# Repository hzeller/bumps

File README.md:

Bumps
=====

> BeagleBone Universal Multi Pololu Steppers

BeagleBone Black cape for [BeagleG][beagleg-url]; using 5 stepper driver modules
from Pololu.

Bumps is an board to work together with [BeagleG][beagleg-url], a fast
GCode system for CNC/3D printers and one of the first making use of the PRU
of the Beaglebone Black for extremely fast step generation.

Find the current version from June 2015 [shared on OshPark][osh-bumps1]. Or use
the [Gerber files](./gerbers/bumps-gerbers.zip) directly.

### Version History

  * Version 0.1 March 2014 ; 5 Stepper drivers, 2 Power PWMs, 2 small PWM, 2 aux outputs.
  * Version 0.2 June 2015; small revision of otherwise great first board (fix a missing pullup and wrong solder-mask at one place).

### Current work
Work in progress on 0.3 hardware update.

Version 0.3 is work in progress with some changed FETs and other little changes
(see illustration below) but also there is a bigger change
(in branch drv8825-direct) work in progress to directly use the drv8825
drivers without Pololu modules.

Features
   * Simple, mostly passive board with cheap components.
   * Single supply; no separate 5V needed:
      * 5V switching supply to power the BeagleBone from motor voltage (12-36V).
      * Local 3.3V power supply to not put any strain on BBB 3.3V
   * 5 slots for [Pololu-compatible][pololu-url] stepper driver boards.
   * 1 Emergency switch input, directly wired to hardware-reset stepper drivers.
   * 2 high power PWM (Motor voltage, ~20A)
   * 2 Open Collector PWM for smaller loads (Up to 20V, ~2A)
   * 2 Open Collector Auxiliary Outputs (Up to 20V, ~2A)
   * 3 endswitch inputs.
   * 3 temperature sensor inputs.

The following illustrations represent the current work in progress:

![Schematic][schem]
![Board][board]

In real life, the March 2014 version (essentially identical to the June 2015
version):

![Assembled][assembled]

  * Board fabbed by http://oshpark.com/
  * Solder paste dispensed with http://github.com/jerkey 's 3D printer, using
	a program to translate a KiCAD file to GCode (https://github.com/hzeller/rpt2paste )
	.. the whole thing made it to Hackaday:
	http://hackaday.com/2014/04/02/dispensing-solder-paste-with-a-3d-printer/
  * Assembled using a self-made vacuum tweezer
	https://plus.google.com/u/0/+HennerZeller/posts/b3NbB7NzQcM
  * Early test of the system http://youtu.be/hIEY9077D64

[beagleg-url]: https://github.com/hzeller/beagleg
[pololu-url]: http://www.pololu.com/product/1182
[schem]: https://github.com/hzeller/bumps/raw/master/img/bumps-schem.png
[board]: https://github.com/hzeller/bumps/raw/master/img/bumps-board.png
[assembled]: https://github.com/hzeller/bumps/raw/master/img/bumps-connect.jpg
[osh-bumps1]: https://oshpark.com/shared_projects/zIXfRqDE

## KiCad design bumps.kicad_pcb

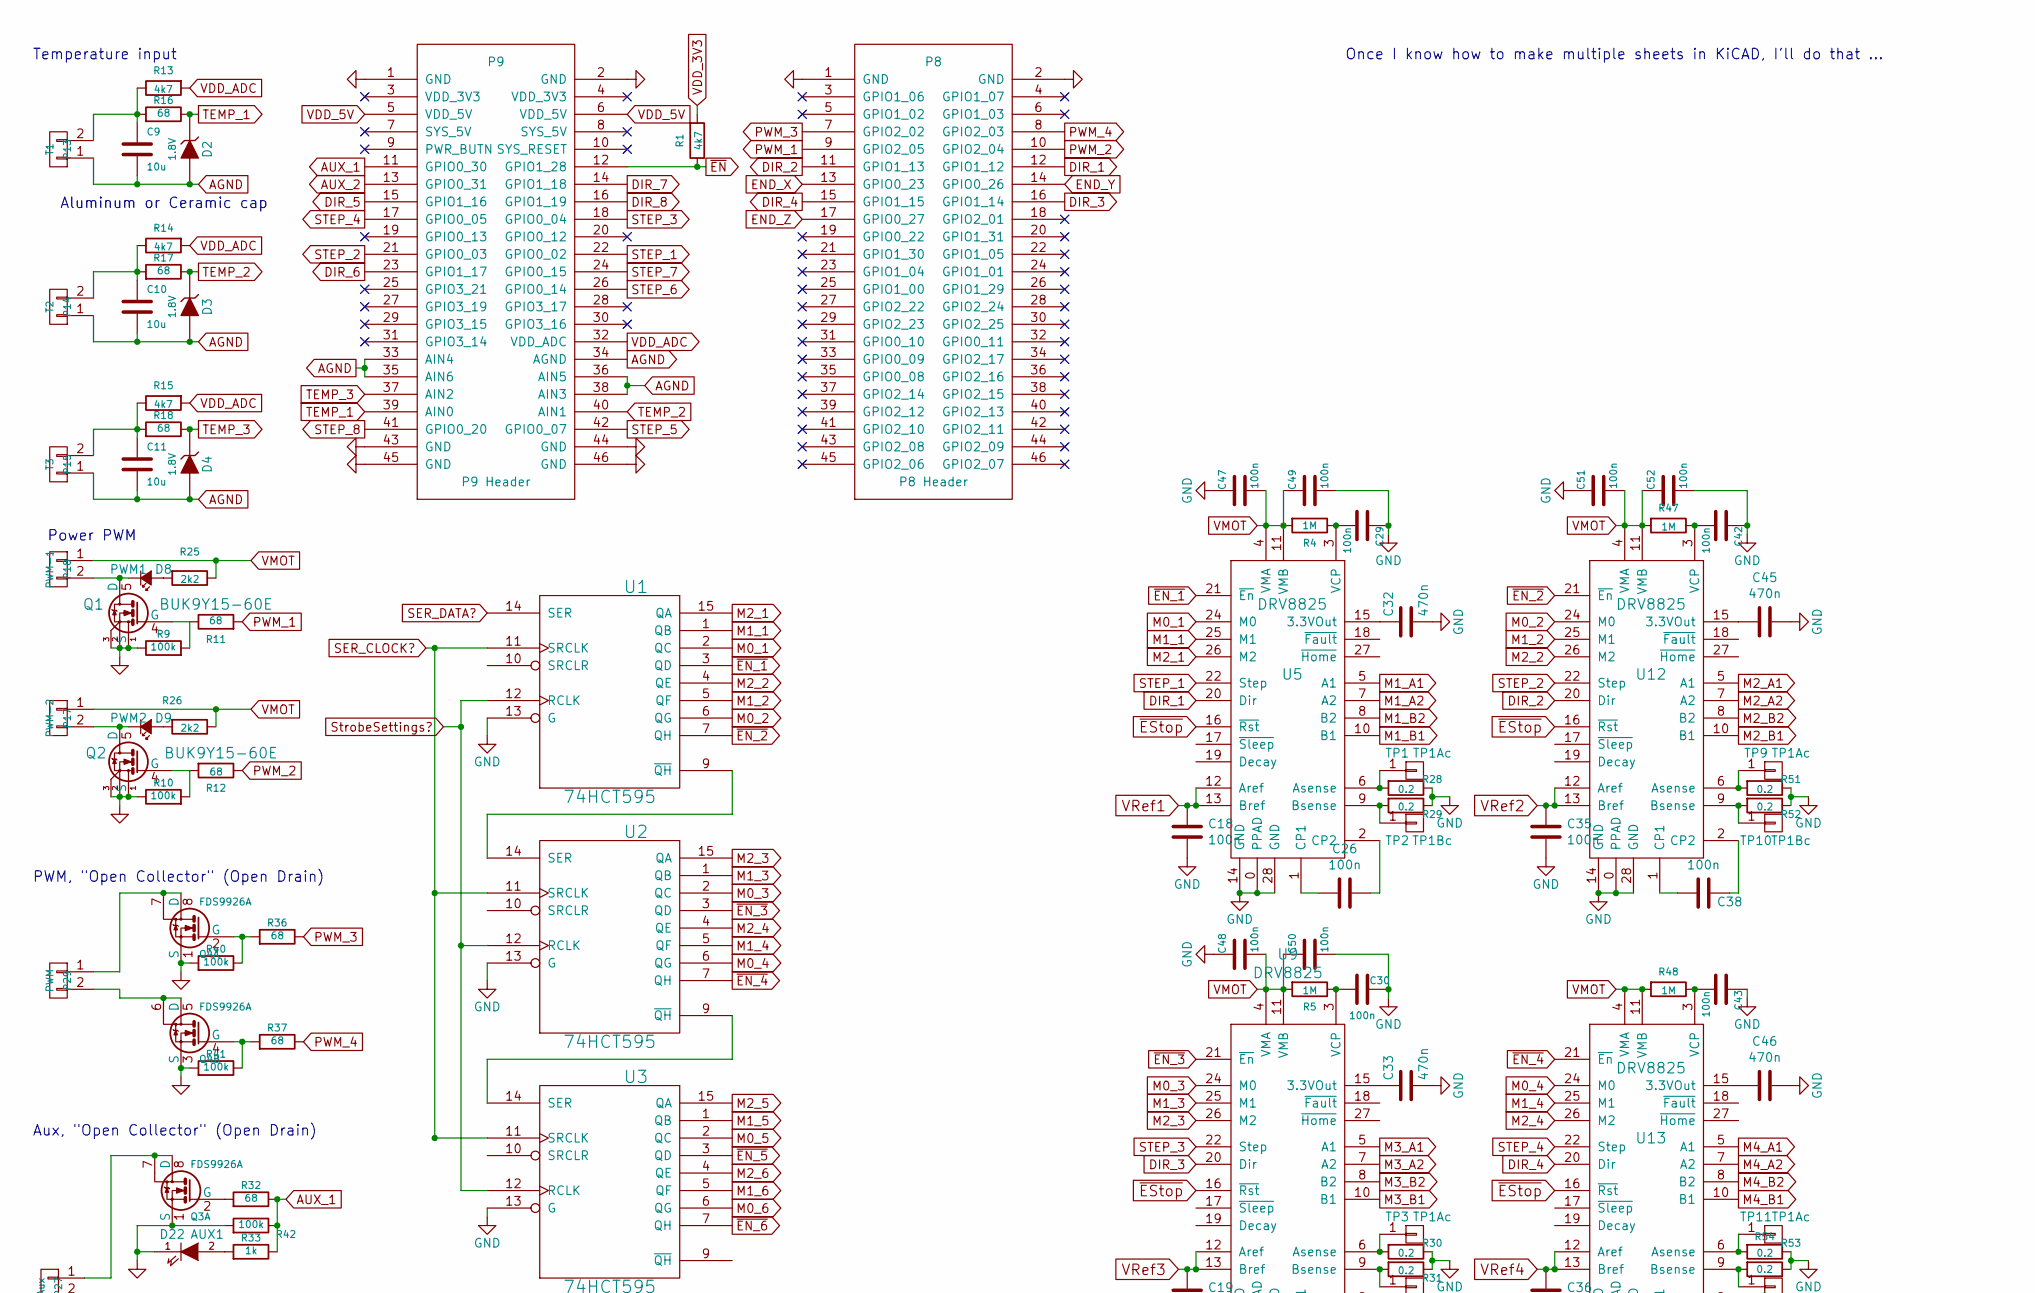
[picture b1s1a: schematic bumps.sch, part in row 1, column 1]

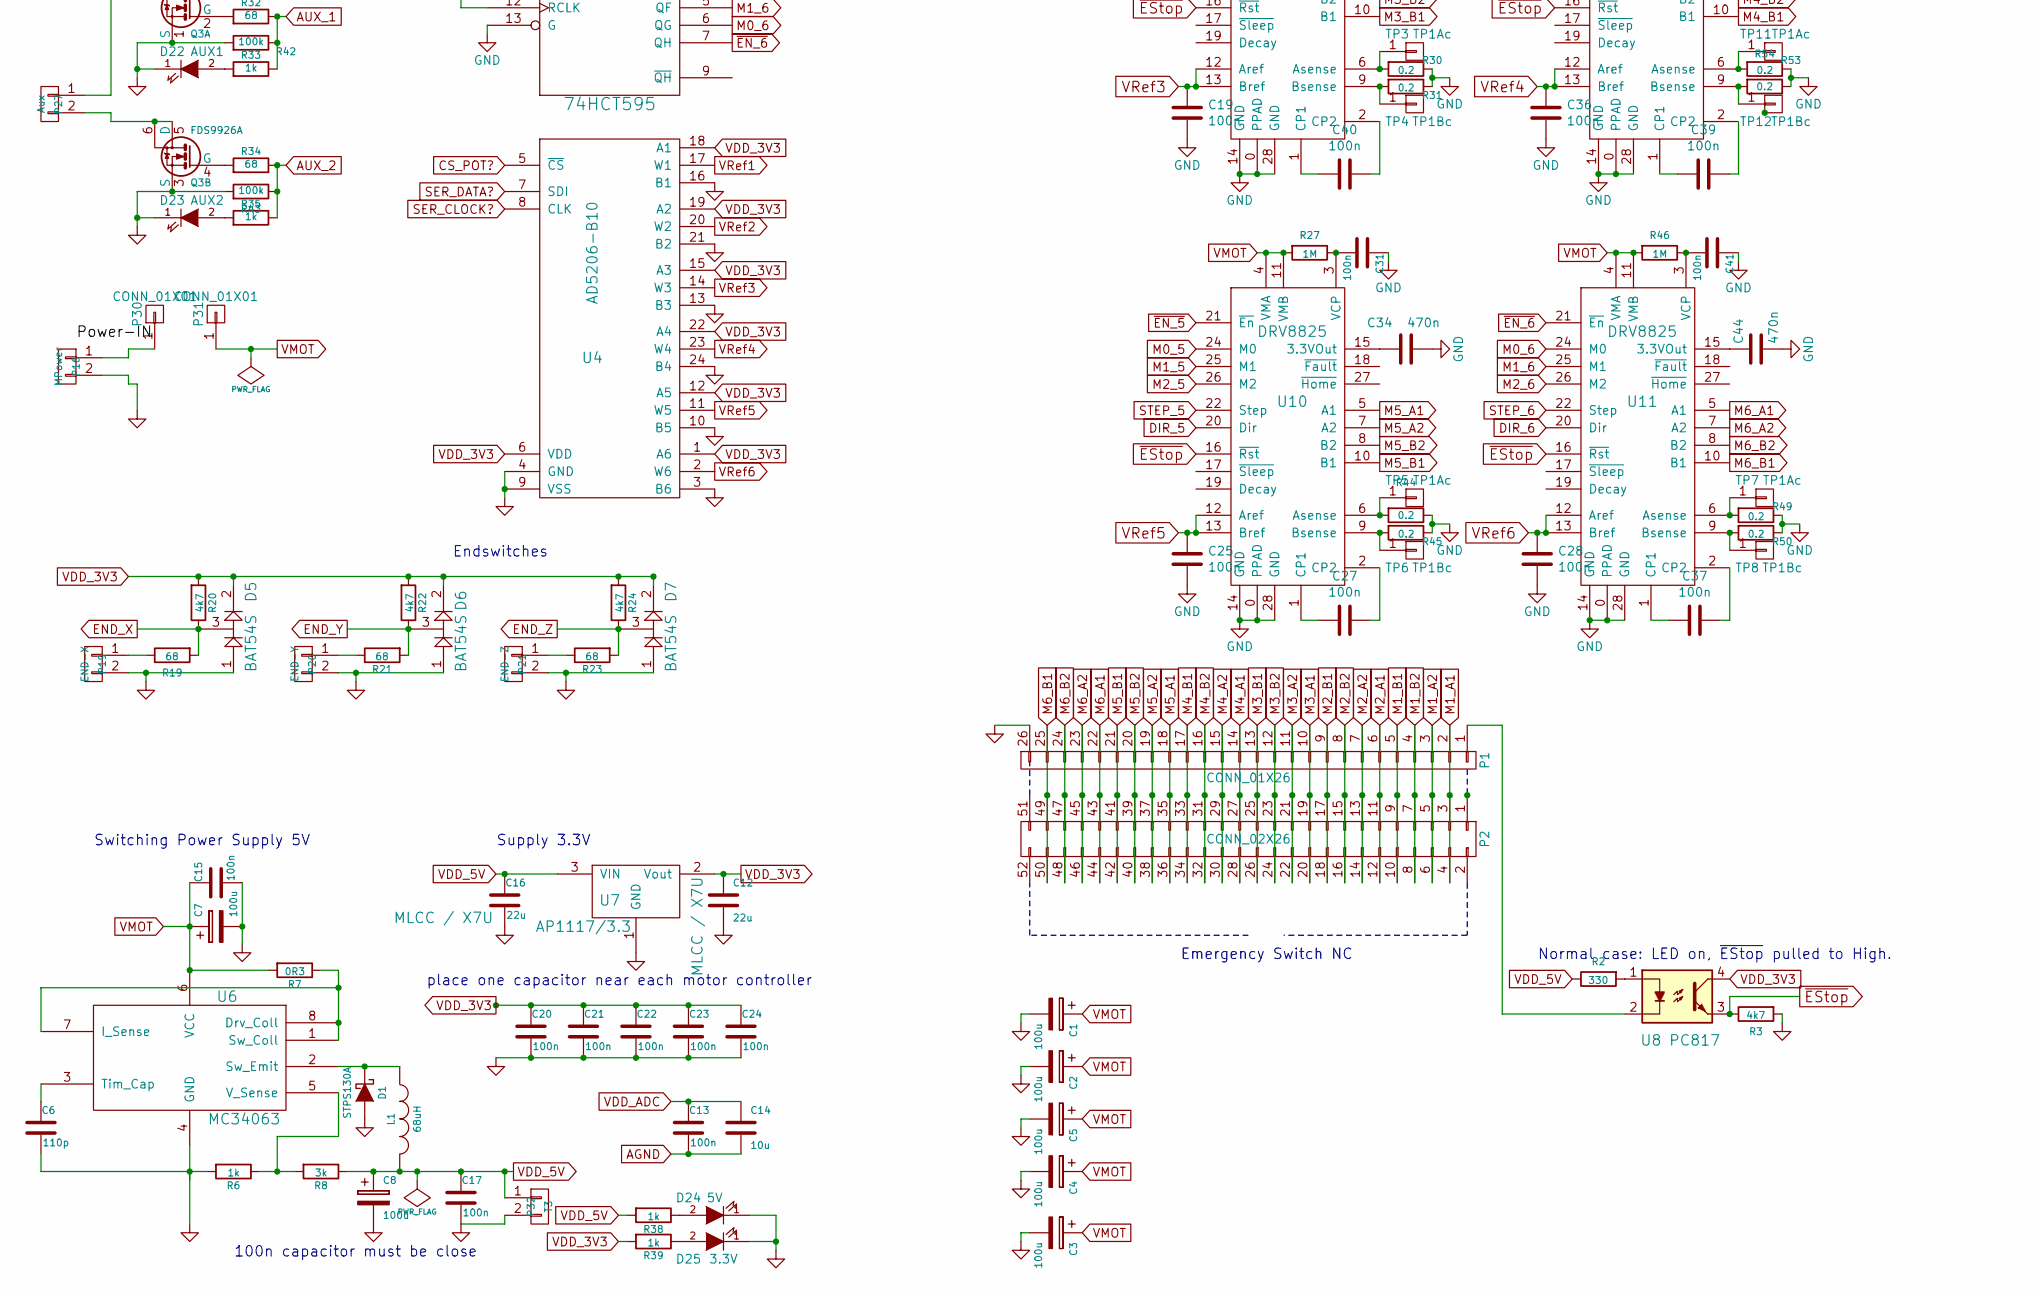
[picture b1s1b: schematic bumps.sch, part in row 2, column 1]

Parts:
C1, C2, C3, C4, C5, C7: 100u; c_elec_6.3x7.7
C6: 110p; C_0805
C8: 100u; C_1206
C9, C10, C11, C14: 10u; C_0805
C12, C16: 22u; C_1206
C13, C15, C17, C20, C21, C22, C23, C24: 100n; C_0805
C18, C19, C25, C26, C27, C28, C29, C30, C31, C35, C36, C37, C38, C39, C40, C41, C42, C43, C47, C48, C49, C50, C51, C52: 100n; C_0603
C32, C33, C34, C44, C45, C46: 470n; C_0603
D1: STPS130A; Diode-SMA_Standard
D2, D3, D4: 1.8V; SOD-123
D5, D6, D7: BAT54S; SOT-23
D8: PWM1; LED-0805
D9: PWM2; LED-0805
D22: AUX1; LED-0805
D23: AUX2; LED-0805
D24: 5V; LED-0805
D25: 3.3V; LED-0805
L1: 68uH; INDUCTOR_V; DigiKey RLB0914-680KL
P1: CONN_01X26; Pin_Header_Straight_1x26
P2: CONN_02X26; Pin_Header_Straight_2x26
P8: P8 Header; PIN_ARRAY_23X2
P9: P9 Header; PIN_ARRAY_23X2
P13: T1; Pin_Header_Straight_1x02
P14: T2; Pin_Header_Straight_1x02
P15, P32: T3; Pin_Header_Straight_1x02
P16: MPower; AK300-2
P17: PWM-2; AK300-2
P18: PWM-1; AK300-2
P19: END-X; Pin_Header_Straight_1x02
P20: END-Y; Pin_Header_Straight_1x02
P21: END-Z; Pin_Header_Straight_1x02
P27: Aux; Pin_Header_Straight_1x02
P29: PWM; Pin_Header_Straight_1x02
P30, P31: CONN_01X01; FuseBlade
Q1, Q2: BUK9Y15-60E; SOT-669_LFPAK_ThermalVias-1
Q3, Q4: FDS9926A; SOIC-8_3.9x4.9mm_Pitch1.27mm
R1, R3, R13, R14, R15, R20, R22, R24: 4k7; R_0805
R2: 330; R_0805
R4, R5, R27, R46, R47, R48: 1M; R_0603
R6, R33, R35, R38, R39: 1k; R_0805
R7: 0R3; R_0805
R8: 3k; R_0805
R9, R10, R40, R41, R42, R43: 100k; R_0805
R11, R12, R16, R17, R18, R19, R21, R23, R32, R34, R36, R37: 68; R_0805
R25, R26: 2k2; R_0805
R28, R29, R30, R31, R44, R45, R49, R50, R51, R52, R53, R54: 0.2; R_1206
TP1, TP3, TP5, TP7, TP9, TP11: TP1Ac; TP
TP2, TP4, TP6, TP8, TP10, TP12: TP1Bc; TP
U1, U2, U3: 74HCT595; TSSOP-16_4.4x5mm_Pitch0.65mm
U4: AD5206-B10; TSSOP-24_4.4x7.8mm_Pitch0.65mm
U5, U9, U10, U11, U12, U13: DRV8825; HTSSOP-28_4.4x9.7mm_Pitch0.65mm
U6: MC34063; SOIC-8_3.9x4.9mm_Pitch1.27mm
U7: AP1117/3.3; SOT-223-3
U8: PC817; DIP-4_W7.62mm

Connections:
AGND: C9.2, C10.2, C11.2, C13.2, C14.2, D2.2 (A), D3.2 (A), D4.2 (A), P9.33 (AIN4), P9.34 (AGND), P9.35 (AIN6), P9.36 (AIN5), P9.38 (AIN3), P13.1, P14.1, P15.1
AUX_1: P9.11 (GPIO0_30), R32.1, R33.1, R42.1
AUX_2: P9.13 (GPIO0_31), R34.1, R35.1, R43.1
DIR_1: P8.12 (GPIO1_12), U5.20 (Dir)
DIR_2: P8.11 (GPIO1_13), U12.20 (Dir)
DIR_3: P8.16 (GPIO1_14), U9.20 (Dir)
DIR_4: P8.15 (GPIO1_15), U13.20 (Dir)
DIR_5: P9.15 (GPIO1_16), U10.20 (Dir)
DIR_6: P9.23 (GPIO1_17), U11.20 (Dir)
END_X: D5.3, P8.13 (GPIO0_23), R19.2, R20.1
END_Y: D6.3, P8.14 (GPIO0_26), R21.2, R22.1
END_Z: D7.3, P8.17 (GPIO0_27), R23.2, R24.1
GND: C1.2, C2.2, C3.2, C4.2, C5.2, C6.2, C7.2, C8.2, C12.2, C15.2, C16.2, C17.2, C18.2, C19.2, C20.2, C21.2, C22.2, C23.2, C24.2, C25.1, C28.1, C29.1, C30.1, C31.1, C32.2, C33.2, C34.2, C35.1, C36.2, C41.1, C42.1, C43.1, C44.2, C45.2, C46.2, C47.1, C48.1, C49.2, C50.2, C51.1, C52.2, D1.2 (A), D5.1, D6.1, D7.1, D22.1 (K), D23.1 (K), D24.1 (K), D25.1 (K), P1.26, P8.1 (GND), P8.2 (GND), P9.1 (GND), P9.2 (GND), P9.43 (GND), P9.44 (GND), P9.45 (GND), P9.46 (GND), P16.2, P19.2, P20.2, P21.2, P32.2, Q1.1 (S), Q1.2, Q1.3, Q2.1 (S), Q2.2, Q2.3, Q3.1 (S), Q3.3 (S), Q4.1 (S), Q4.3 (S), R3.2, R6.2, R9.1, R10.1, R28.1, R29.1, R30.1, R31.1, R40.2, R41.2, R42.2, R43.2, R44.1, R45.1, R49.1, R50.1, R51.1, R52.1, R53.1, R54.1, U1.8 (GND), U1.13 (G), U2.8 (GND), U2.13 (G), U3.8 (GND), U3.13 (G), U4.3 (B6), U4.4 (GND), U4.9 (VSS), U4.10 (B5), U4.13 (B3), U4.16 (B1), U4.21 (B2), U4.24 (B4), U5.0 (PPAD), U5.14 (GND), U5.28 (GND), U6.4 (GND), U7.1 (GND), U9.0 (PPAD), U9.14 (GND), U9.28 (GND), U10.0 (PPAD), U10.14 (GND), U10.28 (GND), U11.0 (PPAD), U11.14 (GND), U11.28 (GND), U12.0 (PPAD), U12.14 (GND), U12.28 (GND), U13.0 (PPAD), U13.14 (GND), U13.28 (GND)
M0_1: U1.2 (QC), U5.24 (M0)
M0_2: U1.6 (QG), U12.24 (M0)
M0_3: U2.2 (QC), U9.24 (M0)
M0_4: U2.6 (QG), U13.24 (M0)
M0_5: U3.2 (QC), U10.24 (M0)
M0_6: U3.6 (QG), U11.24 (M0)
M1_1: U1.1 (QB), U5.25 (M1)
M1_2: U1.5 (QF), U12.25 (M1)
M1_3: U2.1 (QB), U9.25 (M1)
M1_4: U2.5 (QF), U13.25 (M1)
M1_5: U3.1 (QB), U10.25 (M1)
M1_6: U3.5 (QF), U11.25 (M1)
M1_A1: P1.2, P2.3, P2.4, U5.5 (A1)
M1_A2: P1.3, P2.5, P2.6, U5.7 (A2)
M1_B1: P1.5, P2.9, P2.10, U5.10 (B1)
M1_B2: P1.4, P2.7, P2.8, U5.8 (B2)
M2_1: U1.15 (QA), U5.26 (M2)
M2_2: U1.4 (QE), U12.26 (M2)
M2_3: U2.15 (QA), U9.26 (M2)
M2_4: U2.4 (QE), U13.26 (M2)
M2_5: U3.15 (QA), U10.26 (M2)
M2_6: U3.4 (QE), U11.26 (M2)
M2_A1: P1.6, P2.11, P2.12, U12.5 (A1)
M2_A2: P1.7, P2.13, P2.14, U12.7 (A2)
M2_B1: P1.9, P2.17, P2.18, U12.10 (B1)
M2_B2: P1.8, P2.15, P2.16, U12.8 (B2)
M3_A1: P1.10, P2.19, P2.20, U9.5 (A1)
M3_A2: P1.11, P2.21, P2.22, U9.7 (A2)
M3_B1: P1.13, P2.25, P2.26, U9.10 (B1)
M3_B2: P1.12, P2.23, P2.24, U9.8 (B2)
M4_A1: P1.14, P2.27, P2.28, U13.5 (A1)
M4_A2: P1.15, P2.29, P2.30, U13.7 (A2)
M4_B1: P1.17, P2.33, P2.34, U13.10 (B1)
M4_B2: P1.16, P2.31, P2.32, U13.8 (B2)
M5_A1: P1.18, P2.35, P2.36, U10.5 (A1)
M5_A2: P1.19, P2.37, P2.38, U10.7 (A2)
M5_B1: P1.21, P2.41, P2.42, U10.10 (B1)
M5_B2: P1.20, P2.39, P2.40, U10.8 (B2)
M6_A1: P1.22, P2.43, P2.44, U11.5 (A1)
M6_A2: P1.23, P2.45, P2.46, U11.7 (A2)
M6_B1: P1.25, P2.49, P2.50, U11.10 (B1)
M6_B2: P1.24, P2.47, P2.48, U11.8 (B2)
unnamed: C6.1, U6.3 (Tim_Cap)
unnamed: C9.1, P13.2, R13.1, R16.2
unnamed: C10.1, P14.2, R14.1, R17.2
unnamed: C11.1, P15.2, R15.1, R18.2
unnamed: C26.1, U5.2 (CP2)
unnamed: C26.2, U5.1 (CP1)
unnamed: C27.1, U10.2 (CP2)
unnamed: C27.2, U10.1 (CP1)
unnamed: C29.2, R4.1, U5.3 (VCP)
unnamed: C30.2, R5.1, U9.3 (VCP)
unnamed: C31.2, R27.1, U10.3 (VCP)
unnamed: C32.1, U5.15 (3.3VOut)
unnamed: C33.1, U9.15 (3.3VOut)
unnamed: C34.1, U10.15 (3.3VOut)
unnamed: C37.1, U11.1 (CP1)
unnamed: C37.2, U11.2 (CP2)
unnamed: C38.1, U12.2 (CP2)
unnamed: C38.2, U12.1 (CP1)
unnamed: C39.1, U13.1 (CP1)
unnamed: C39.2, U13.2 (CP2)
unnamed: C40.1, U9.1 (CP1)
unnamed: C40.2, U9.2 (CP2)
unnamed: C41.2, R46.1, U11.3 (VCP)
unnamed: C42.2, R47.1, U12.3 (VCP)
unnamed: C43.2, R48.1, U13.3 (VCP)
unnamed: C44.1, U11.15 (3.3VOut)
unnamed: C45.1, U12.15 (3.3VOut)
unnamed: C46.1, U13.15 (3.3VOut)
unnamed: D1.1 (K), L1.1, U6.2 (Sw_Emit)
unnamed: D8.1 (K), P18.2, Q1.5 (D)
unnamed: D8.2 (A), R25.2
unnamed: D9.1 (K), P17.2, Q2.5 (D)
unnamed: D9.2 (A), R26.2
unnamed: D22.2 (A), R33.2
unnamed: D23.2 (A), R35.2
unnamed: D24.2 (A), R38.1
unnamed: D25.2 (A), R39.1
unnamed: P1.1, U8.2
unnamed: P16.1, P30.1
unnamed: P19.1, R19.1
unnamed: P20.1, R21.1
unnamed: P21.1, R23.1
unnamed: P27.1, Q3.7, Q3.8 (D)
unnamed: P27.2, Q3.5 (D), Q3.6
unnamed: P29.1, Q4.7, Q4.8 (D)
unnamed: P29.2, Q4.5 (D), Q4.6
unnamed: Q1.4 (G), R9.2, R11.1
unnamed: Q2.4 (G), R10.2, R12.2
unnamed: Q3.2 (G), R32.2
unnamed: Q3.4 (G), R34.2
unnamed: Q4.2 (G), R36.2, R40.1
unnamed: Q4.4 (G), R37.2, R41.1
unnamed: R2.2, U8.1
unnamed: R6.1, R8.2, U6.5 (V_Sense)
unnamed: R7.1, U6.1 (Sw_Coll), U6.7 (I_Sense), U6.8 (Drv_Coll)
unnamed: R28.2, TP1.1, U5.6 (Asense)
unnamed: R29.2, TP2.1, U5.9 (Bsense)
unnamed: R30.2, TP3.1, U9.6 (Asense)
unnamed: R31.2, TP4.1, U9.9 (Bsense)
unnamed: R44.2, TP5.1, U10.6 (Asense)
unnamed: R45.2, TP6.1, U10.9 (Bsense)
unnamed: R49.2, TP7.1, U11.6 (Asense)
unnamed: R50.2, TP8.1, U11.9 (Bsense)
unnamed: R51.2, TP9.1, U12.6 (Asense)
unnamed: R52.2, TP10.1, U12.9 (Bsense)
unnamed: R53.2, TP11.1, U13.6 (Asense)
unnamed: R54.2, TP12.1, U13.9 (Bsense)
unnamed: U1.9 (~QH), U2.14 (SER)
unnamed: U2.9 (~QH), U3.14 (SER)
PWM_1: P8.9 (GPIO2_05), R11.2
PWM_2: P8.10 (GPIO2_04), R12.1
PWM_3: P8.7 (GPIO2_02), R36.1
PWM_4: P8.8 (GPIO2_03), R37.1
SER_CLOCK?: U1.11 (SRCLK), U2.11 (SRCLK), U3.11 (SRCLK), U4.8 (CLK)
SER_DATA?: U1.14 (SER), U4.7 (SDI)
STEP_1: P9.22 (GPIO0_02), U5.22 (Step)
STEP_2: P9.21 (GPIO0_03), U12.22 (Step)
STEP_3: P9.18 (GPIO0_04), U9.22 (Step)
STEP_4: P9.17 (GPIO0_05), U13.22 (Step)
STEP_5: P9.42 (GPIO0_07), U10.22 (Step)
STEP_6: P9.26 (GPIO0_14), U11.22 (Step)
StrobeSettings?: U1.12 (RCLK), U2.12 (RCLK), U3.12 (RCLK)
TEMP_1: D2.1 (K), P9.39 (AIN0), R16.1
TEMP_2: D3.1 (K), P9.40 (AIN1), R17.1
TEMP_3: D4.1 (K), P9.37 (AIN2), R18.1
VCC: U1.16 (VCC), U2.16 (VCC), U3.16 (VCC)
VDD_3V3: C12.1, C20.1, C21.1, C22.1, C23.1, C24.1, D5.2, D6.2, D7.2, R1.2, R20.2, R22.2, R24.2, R39.2, U4.1 (A6), U4.6 (VDD), U4.12 (A5), U4.15 (A3), U4.18 (A1), U4.19 (A2), U4.22 (A4), U7.2 (Vout), U8.4
VDD_5V: C8.1, C16.1, C17.1, L1.2, P9.5 (VDD_5V), P9.6 (VDD_5V), P32.1, R2.1, R8.1, R38.2, U7.3 (VIN)
VDD_ADC: C13.1, C14.1, P9.32 (VDD_ADC), R13.2, R14.2, R15.2
VMOT: C1.1, C2.1, C3.1, C4.1, C5.1, C7.1, C15.1, C47.2, C48.2, C49.1, C50.1, C51.2, C52.1, P17.1, P18.1, P31.1, R4.2, R5.2, R7.2, R25.1, R26.1, R27.2, R46.2, R47.2, R48.2, U5.4 (VMA), U5.11 (VMB), U6.6 (VCC), U9.4 (VMA), U9.11 (VMB), U10.4 (VMA), U10.11 (VMB), U11.4 (VMA), U11.11 (VMB), U12.4 (VMA), U12.11 (VMB), U13.4 (VMA), U13.11 (VMB)
VRef1: C18.1, U4.17 (W1), U5.12 (Aref), U5.13 (Bref)
VRef2: C35.2, U4.20 (W2), U12.12 (Aref), U12.13 (Bref)
VRef3: C19.1, U4.14 (W3), U9.12 (Aref), U9.13 (Bref)
VRef4: C36.1, U4.23 (W4), U13.12 (Aref), U13.13 (Bref)
VRef5: C25.2, U4.11 (W5), U10.12 (Aref), U10.13 (Bref)
VRef6: C28.2, U4.2 (W6), U11.12 (Aref), U11.13 (Bref)
~EN: P9.12 (GPIO1_28), R1.1
~EN_1: U1.3 (QD), U5.21 (~En)
~EN_2: U1.7 (QH), U12.21 (~En)
~EN_3: U2.3 (QD), U9.21 (~En)
~EN_4: U2.7 (QH), U13.21 (~En)
~EN_5: U3.3 (QD), U10.21 (~En)
~EN_6: U3.7 (QH), U11.21 (~En)
~EStop: R3.1, U5.16 (~Rst), U8.3, U9.16 (~Rst), U10.16 (~Rst), U11.16 (~Rst), U12.16 (~Rst), U13.16 (~Rst)

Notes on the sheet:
Aux, "Open Collector" (Open Drain)
PWM, "Open Collector" (Open Drain)
Power PWM
Temperature input
Switching Power Supply 5V
Supply 3.3V
Endswitches
place one capacitor near each motor controller
100n capacitor must be close
Aluminum or Ceramic cap
Normal case: LED on, ~EStop~ pulled to High.
Emergency Switch NC
Once I know how to make multiple sheets in KiCAD, I'll do that ...

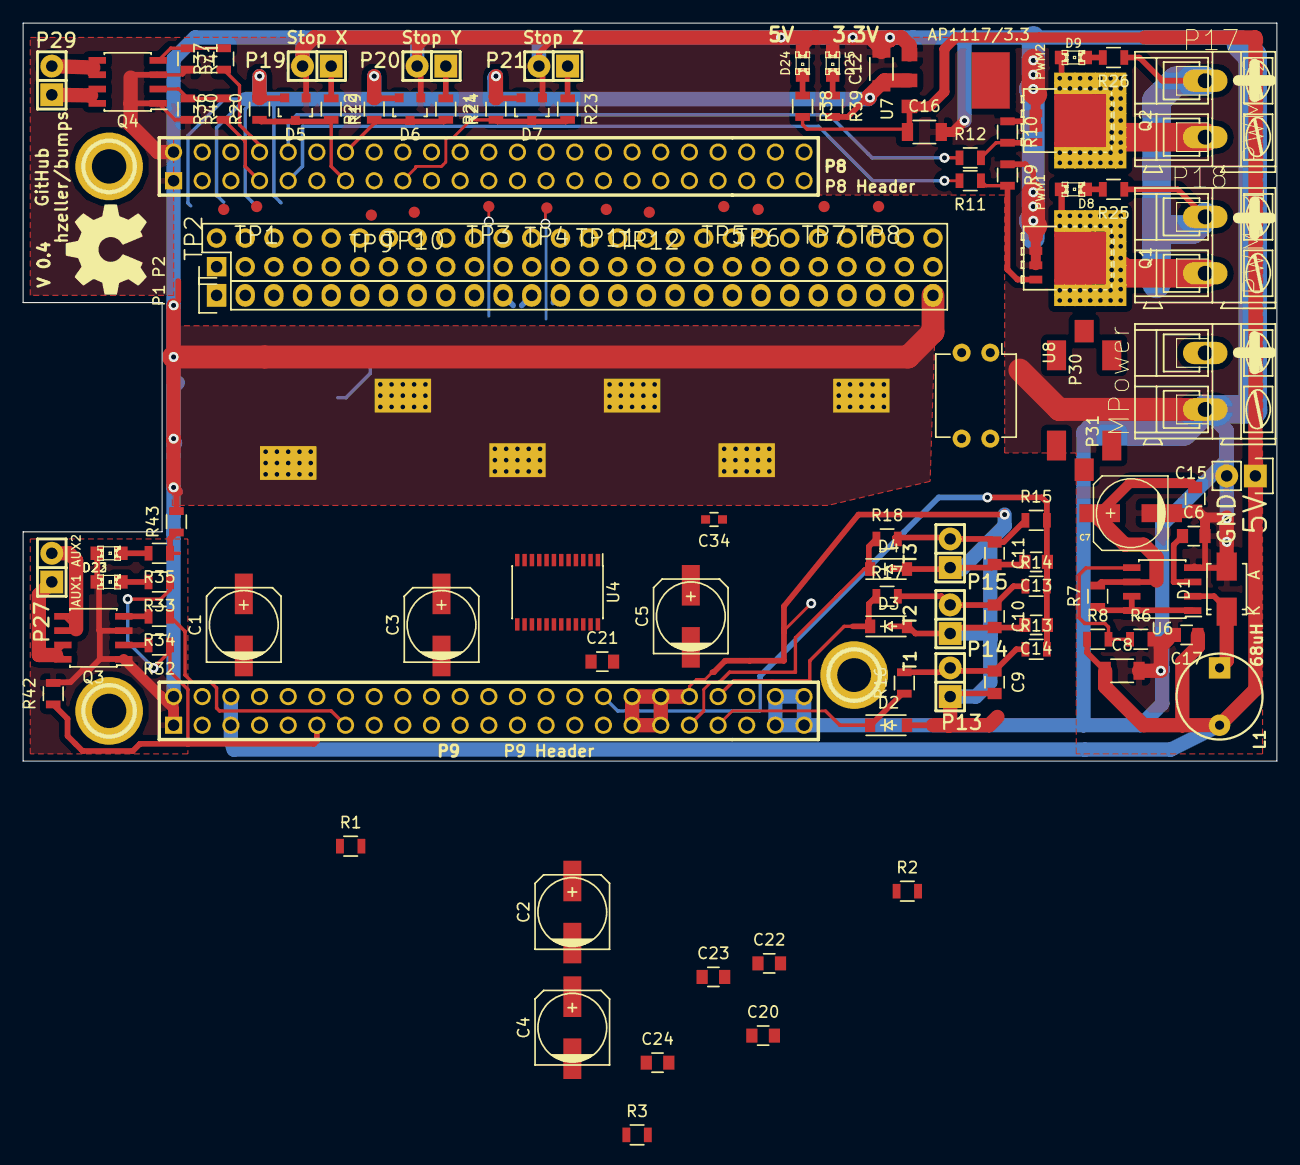
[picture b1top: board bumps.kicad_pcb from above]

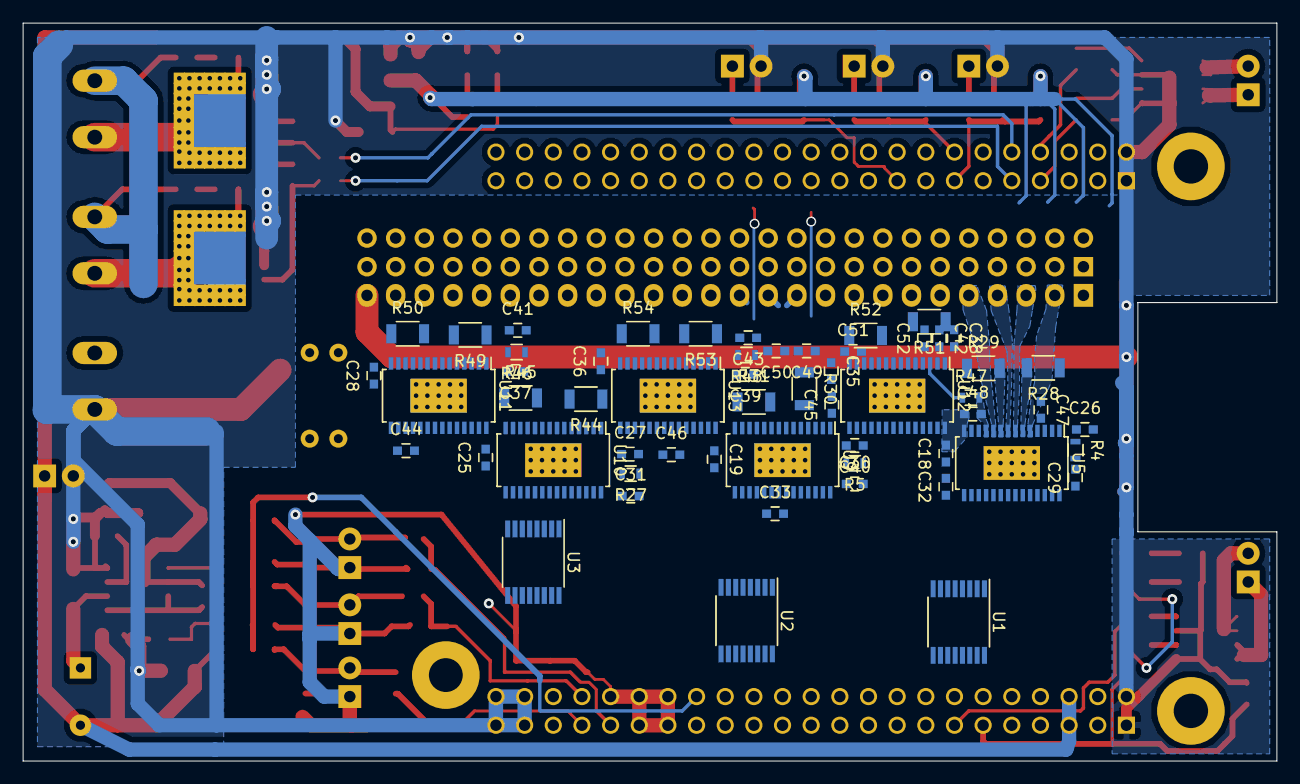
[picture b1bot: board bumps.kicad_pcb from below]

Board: 2 copper layers, 111.1 x 65.4 mm, 170 parts (56 on the bottom side), 159 nets.

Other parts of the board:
M1, M2, M3: CONN_1; 1pin

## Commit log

2014-02-02 Init working on a BeagleBone Pololu driver board
2014-02-02 o Add step/dir signals.
2014-02-02 added bumps.mod footprints file and set footprints in schematic
2014-02-02 moved origin in PIN_ARRAY_23X2 to be centered on a pin, for lining up with grid
2014-02-02 o association of schematic->footprint.
2014-02-02 added board in kicad 2012-oct-18 and placed parts and board edges and ethernet cutout
2014-02-02 o Add end-switches and one capacitor.
2014-02-02 added lots of traces AND SWAPPED POSITIONS OF TWO POLOLUS
2014-02-02 o Add FETs, Power Input.
2014-02-02 o more generic fet name.
2014-02-02 o Add voltage regulator: generate 5V out of motor voltage.
2014-02-02 o Switch off footprint visibility.
2014-02-02 o Add output capacitor for 5V supply. o Give values to pololu input caps.
2014-02-02 o Random changes kicad did to the project file.
2014-02-02 o Add a little more explanation in README.
2014-02-02 o update readme.
2014-02-02 o Nicer layout of PWM circuit. o Make sure that PWM FET is pulled down properly and protect BBB output from Gate capacitor switching current.
2014-02-02 o update schematic image.
2014-02-03 o a bit more realistic capacitor footprint.
2014-02-04 o add isolator library.
2014-02-04 o add isolator library. (Attribution: https://github.com/OpenElectronicsLab/eeg-mouse )
2014-02-04 o Not using isolators for now.
2014-02-04 o remove reference to isolators lib.
2014-02-04 o Add analog inputs with input protection. o add input protection to end switches. o Add LDO to create a local 3.3V from 5V; use that everywhere, don't use 3.3V provided by BBB o Add LEDs to heater P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
2014-02-04 o Remove footprint overlay for new components. o Update schematic image.
2014-02-04 o remove ghost window.
2014-02-04 o Make wiring of temp-sensor look less crowded. o add testpoints for 3.3V and 5V o Ground all the BBB grounds.
2014-02-05 o Latest schematic image.
2014-02-08 o Make labels not overlap each other (50mil text size instead of 60mil).
2014-02-08 o Move some labels for better readability.
2014-02-17 o updating the schematic with smallish changes.
2014-02-17 o Add sot-223-3 footprint
2014-02-17 o re-import footprints.
2014-02-17 o new board version.
2014-02-17 o Separate out the two connectors for motors. o Add free-running diode for PWM connector.
2014-02-17 o Direction LEDs o Footprints changed. o instad of 120u, use 100u for keeping the BOM small.
2014-02-17 o placing work in progres...
2014-02-17 o Add 100n for VMOT in to 34063
2014-02-17 o Don't show obnoxious footprints.
2014-02-17 o import 100n VMOT cap.
2014-02-17 o Some random change kicad generated.
2014-02-21 o Some better naming of LEDs
2014-02-21 o Rough initial placement.
2014-02-22 o turn around micro-step jumper headers. o more appropriate LED footprints.
2014-02-23 o Return accidentally moved global label.
2014-03-02 o More placing. o Add Open Collector AUX and PWM for independent use. o Re-arrange end-switch for easier placement.
2014-03-03 o Initital placement.
2014-03-03 o First routings. o Update README, schematic image.
2014-03-03 o Qualify useful voltage.
2014-03-03 o Analog part routed.
2014-03-03 o Better cut-out for ethernet.
2014-03-03 o Swap power-in, so that polarity is consistent with PWM outs.
2014-03-03 o Yet more space for ethernet connector.
2014-03-04 o Add analog ground plane on top layer.
2014-03-04 o Make analog zone more compact, so that we have place to wire through VMOT
2014-03-04 o First version basic power busses.
2014-03-04 o A little bit more clearance for traces near ethernet.
2014-03-04 o One more ground connector.
2014-03-04 o Add description to endswitch-section.
2014-03-04 o Update schema image.
2014-03-04 o Add OSH logo.
2014-03-04 o Smallish tweaks.
2014-03-04 o wire up aux1, aux2
2014-03-04 o Starting 'wire accross board'-puzzle: all the signals that are inconveniently connecting on opposite sides of the board.
2014-03-04 o Wire up Step-X, Step-Y, Dir-E
2014-03-05 o More signals routed.
2014-03-05 o Wire up stepX and ~EN
2014-03-05 o wire up some simple signals.
2014-03-05 o some no-op (I think - whatever kicad thought to change).
2014-03-06 changed the ground Zone around C9 C10 C11 (thermistor caps) to 'thermals' to make it easier to solder the caps (buildability issue)
2014-03-06 o Solve 3.3V connect between two areas.
2014-03-06 o A bit more symmetrical 3.3V solution.
2014-03-06 o readme clarification.
2014-03-06 o connect power PWM o start GND plane.
2014-03-06 o more GND planes.
2014-03-06 o Some updates of labels.
2014-03-06 o Add board reference.
2014-03-06 o Straighten out motor power trace to lower part a bit.
2014-03-06 o update board image.
2014-03-06 add resistors in parallel with aux1 and aux2 LEDs to turn off FETs when not asserted high by CPU
2014-03-06 change resistor values for 5V and 3.3V LEDs to make them indicators not eye burners
2014-03-06 change LED resistors and add lots of necessary bypass capacitors
2014-03-06 fix capacitors on 5V and 3,3V LEDs to be connected properly across resistors
2014-03-06 o Straighten out some wires (easier to grab for operations) o connect 100K Gate resistor directly to gound. Easier to layout.
2014-03-06 o smallish label updates.
2014-03-07 o don't use VMOT 100n caps for now.
2014-03-07 o Annotate new components.
2014-03-07 o fix moved GND pin.
2014-03-07 o Route the new capacitors and resistors.
2014-03-07 o More copper around pads - fuse - mounting holes.
2014-03-07 o ..
2014-03-07 o Update images.
2014-03-07 o Move designators around so that they are more readable.
2014-03-07 o add bottom mask layer.
2014-03-07 o add script to create osh-park compatible file-names
2014-03-08 o Screwup in screw-terminals: they didn't have a B-Mask (doh), and also had F-paste. Sounds like someone designed that as SMD pad.
2014-03-08 o Add remark that analog input cap can as well be ceramic.
2014-03-10 o Smallish adpations while finishing the BOM - some improved placements of designators/values on board - use standard 0805 component for capacitor (not the capacitor 0805)
2014-03-10 o Remove footprint labels in schema.
2014-03-11 o More production output settings.
2014-03-11 o Simplify fab generation. o include bottom solder mask.
2014-04-05 o Add physical image.
2014-04-05 o describe assembly process
2014-04-05 o tweaks.
2015-05-07 o Fix components, that disappeared in the kicad library (CONN_1, CONN_2 and CONN_4 don't exist anymore, they are now CONN_01X01, CONN_01X02 and CONN_01x04). o Connect the new components that inconven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
2015-06-03 o Add gitignore.
2015-06-03 o Re-read net file for board; new version of kicad now removes empty nets.
2015-06-03 o Get rid of 100k pull-down for MS1. Not needed (fixes #9)
2015-06-03 o Use 10uF ceramic capacitors in analog section. Makes that part more compact and nicer to assemble. Fixes #7
2015-06-03 o Add 4k7 pullup to ~Enable o Version number on board-text bumped to v0.2 o Addresses 'enable' part of issue #4
2015-06-03 o Change footprint of power-FET to have the heat-sink on the right side. o Addresses part of issue #4
2015-06-03 o Rename motor labels from 'Polo X' to 'Motor 1'. The axis assignment is not done in the hardware, but can be freely assigned in the software. So this would be confusing.
2015-06-03 o Put all motor connectors in a line (not wiggly line anymore) o Have distance between the same motor connectors 0.2" (distance in female dual sided edge connector) o Fixes #5
2015-06-03 o Update current images
2015-06-03 o Remove grid.
2015-06-03 o straighten some traces, and user thicker traces where possible.
2015-06-04 o little re-arrange stuff and add start of EStop input.
2015-06-04 o convert library to .pretty o add DIL-4 for OptoCoupler (Didn't find it in lib?) and 0.2" distance Wide header for the Estop switch. o assignement and import into pcb, but not routed yet. o make a b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
2015-06-04 o Add fp-lib-table, now needed.
2015-06-04 o Add new layers.
2015-06-05 o Adding fuse holder (footprint and schematic). o .. work in progress. Attempt to make things fit.
2015-06-05 o intermediate state.
2015-06-06 o Bring to latest state of kicad library. o Now checking in also bumps-cache: learned that it is effectively the 'project library' keeping track of the symbols being used. o (was done in a branch, sq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
2015-06-06 o use standard opto PC817 footprint.
2015-06-06 o Use some current standard components.
2015-06-06 o More standard footprint conversions.
2015-06-07 o Design for Manufacturing: choose the same kind of diode for the switching power supply and the snubber diode to reduce different component BOM count.
2015-06-07 o Use BUK9Y43 as power PWM transistor. SMD is easier to solder.
2015-06-07 o Update used transistor (60V, 15mOhm, > 50A)
2015-06-07 o More compact power supply corner.
2015-06-07 o Have a header for 5V, which could be used as separate 5v input (if DC/DC converter to populated), or as output for smallish loads. Fixes #6
2015-06-07 o Mirror Power PWM block, so that the connectors align with the other board connectors on the left. o Update revision number in sheets.
2015-06-07 o transitional README update.
2015-06-11 o Replace some smallish aluminum caps with MLCCs
2015-06-11 o Don't keep mounting holes on schematic, just make them locked footprints on the board.
2015-06-11 o More compact 3.3V regulator section to prepare for more endswitch components.
2015-06-12 o Add fiducials
2015-06-13 o Update images of work-in-progress
2015-06-24 o Change fiducials.
2015-09-29 Fixed typographical error, changed auxilliary to auxiliary in README.
2015-12-13 o Add DRV8825 to library.
2015-12-14 o basic outline.
2015-12-14 o playing with placement.
2015-12-14 o Add Osh Park link.
2015-12-14 o Update readme
2015-12-14 o Add Makefile and script to create gerber files directly with the new KiCAD Python interface.
2015-12-14 o Add toplevel makefile.
2015-12-14 o Fix typo.
2015-12-14 o Bump version number on silkscreen for work-in-progress version.
2015-12-14 o Let's make drv8825 the 0.4 version.
2016-01-01 o Some rough placement of the DRV8825 (under the board so that we can get rid of heat on the top.
2016-01-01 o more placement experiments.
2016-01-02 o add HTSSOP package (TSSOP with heat pad)
2016-01-25 o Readme update for this branch.

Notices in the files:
bumps.kicad_pcb:
License: CC-BY-SA
